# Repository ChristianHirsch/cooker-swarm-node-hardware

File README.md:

# cooker-swarm-node-hardware

This piece of hardware is used to control a induction hob remotely using a single board computer, a PC/notebook or a smartphone via Bluetooth Low Energy (BLE).

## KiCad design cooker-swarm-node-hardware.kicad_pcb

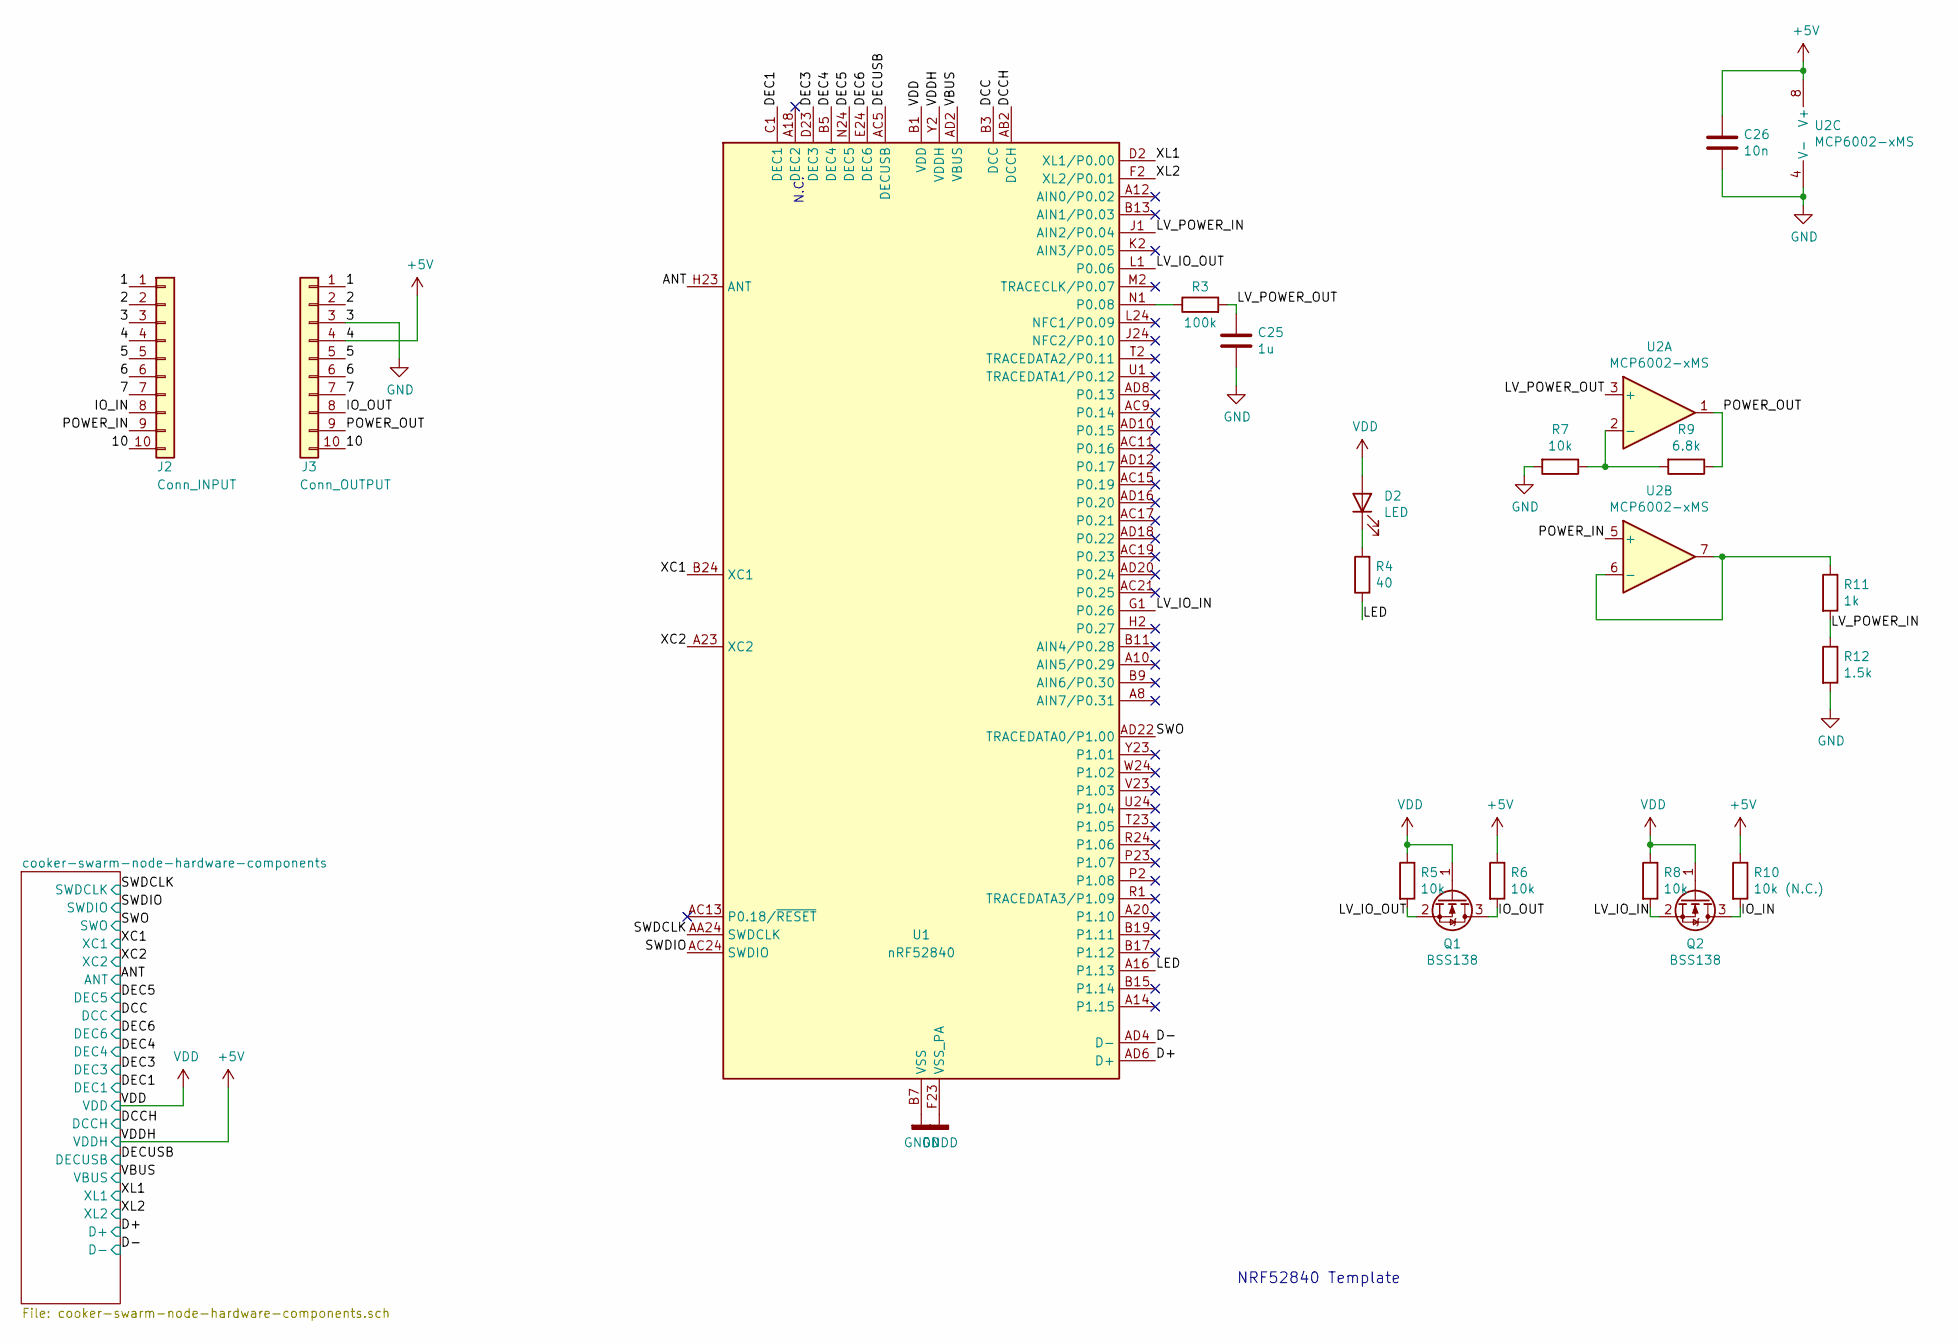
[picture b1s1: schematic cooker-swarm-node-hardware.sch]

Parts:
C25: 1u; C_0603_1608Metric
C26: 10n; C_0402_1005Metric
D2: LED; LED_1206_3216Metric
J2: Conn_INPUT; PinHeader_1x10_P2.54mm_Vertical
J3: Conn_OUTPUT; PinSocket_1x10_P2.54mm_Vertical
Q1, Q2: BSS138; SOT-23
R3: 100k; R_0402_1005Metric
R4: 40; R_0402_1005Metric
R5, R6, R7, R8: 10k; R_0402_1005Metric
R9: 6.8k; R_0402_1005Metric
R10: 10k (N.C.); R_0402_1005Metric
R11: 1k; R_0402_1005Metric
R12: 1.5k; R_0402_1005Metric
U1: nRF52840; Nordic_AQFN-73-1EP_7x7mm_P0.5mm
U2: MCP6002-xMS; MSOP-8_3x3mm_P0.65mm

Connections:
+5V: C26.1, J2.4, J3.4, R6.1, R10.1, U1.Y2 (VDDH), U2.8 (V+); also elsewhere on the board
/1: J2.1, J3.1
/2: J2.2, J3.2
/5: J2.5, J3.5
/6: J2.6, J3.6
/7: J2.7, J3.7
/10: J2.10, J3.10
/ANT: U1.H23 (ANT); also elsewhere on the board
/D+: U1.AD6 (D+); also elsewhere on the board
/D-: U1.AD4 (D-); also elsewhere on the board
/DCC: U1.B3 (DCC); also elsewhere on the board
/DCCH: U1.AB2 (DCCH); also elsewhere on the board
/DEC1: U1.C1 (DEC1); also elsewhere on the board
/DEC3: U1.D23 (DEC3); also elsewhere on the board
/DEC4: U1.B5 (DEC4), U1.E24 (DEC6); also elsewhere on the board
/DEC5: U1.N24 (DEC5); also elsewhere on the board
/DECUSB: U1.AC5 (DECUSB); also elsewhere on the board
/IO_IN: J2.8, Q2.3 (D), R10.2
/IO_OUT: J3.8, Q1.3 (D), R6.2
/LED: R4.1, U1.A16 (P1.13)
/LV_IO_IN: Q2.2 (S), R8.2, U1.G1 (P0.26)
/LV_IO_OUT: Q1.2 (S), R5.2, U1.L1 (P0.06)
/LV_POWER_IN: R11.2, R12.1, U1.J1 (AIN2/P0.04)
/LV_POWER_OUT: C25.1, R3.2, U2.3 (+)
/POWER_IN: J2.9, U2.5 (+)
/POWER_OUT: J3.9, R9.1, U2.1
/SWDCLK: U1.AA24 (SWDCLK); also elsewhere on the board
/SWDIO: U1.AC24 (SWDIO); also elsewhere on the board
/SWO: U1.AD22 (TRACEDATA0/P1.00); also elsewhere on the board
/XC1: U1.B24 (XC1); also elsewhere on the board
/XC2: U1.A23 (XC2); also elsewhere on the board
/XL1: U1.D2 (XL1/P0.00); also elsewhere on the board
/XL2: U1.F2 (XL2/P0.01); also elsewhere on the board
GND: C25.2, C26.2, J2.3, J3.3, R7.2, R12.2, U1.B7 (VSS), U1.EP (VSS), U1.F23 (VSS_PA), U2.4 (V-); also elsewhere on the board
unnamed: D2.1 (K), R4.2
unnamed: R3.1, U1.N1 (P0.08)
unnamed: R7.1, R9.2, U2.2 (-)
unnamed: R11.1, U2.6 (-), U2.7
VBUS: U1.AD2 (VBUS); also elsewhere on the board
VCC: D2.2 (A), Q1.1 (G), Q2.1 (G), R5.1, R8.1, U1.A22 (VDD), U1.AD14 (VDD), U1.AD23 (VDD), U1.B1 (VDD), U1.W1 (VDD); also elsewhere on the board

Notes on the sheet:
NRF52840 Template
N.C.

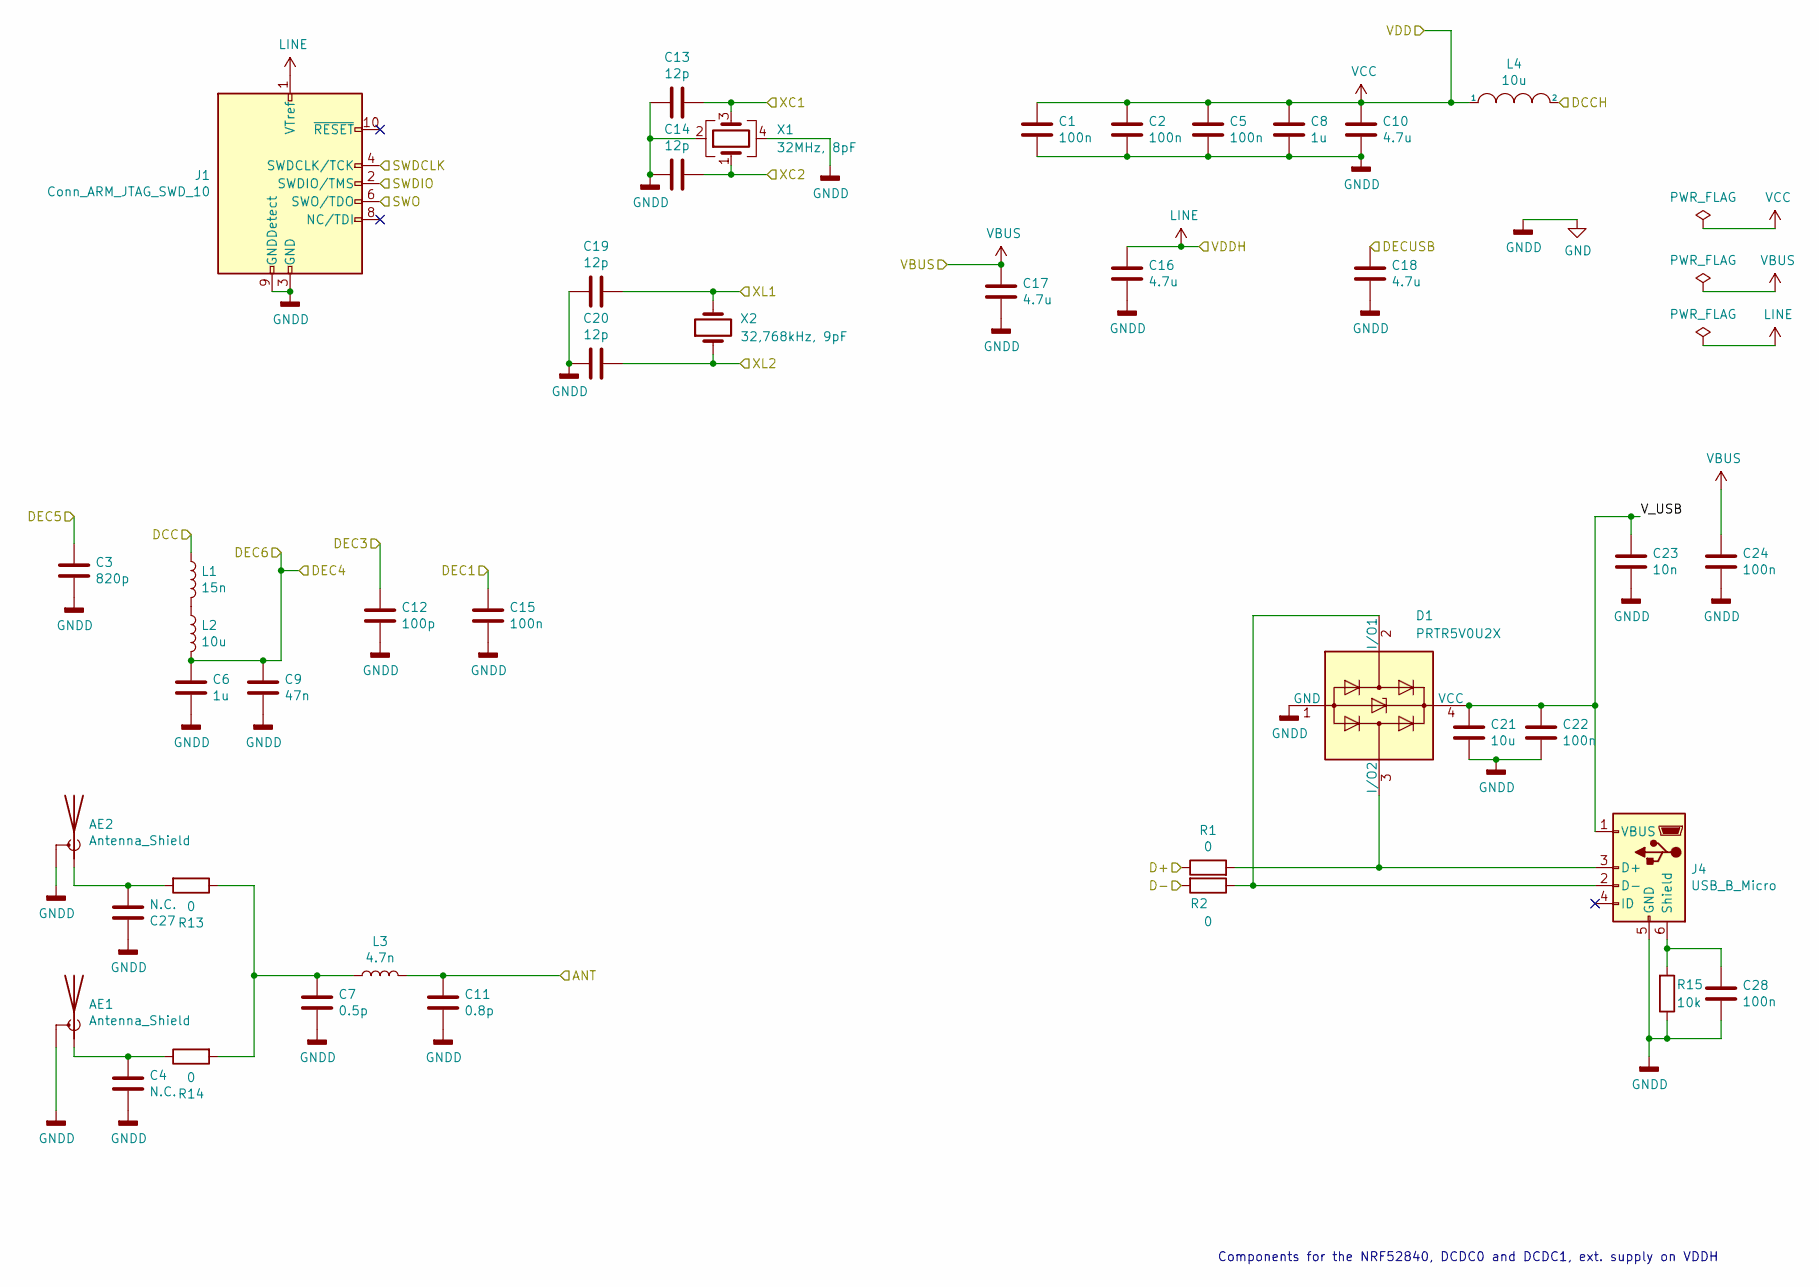
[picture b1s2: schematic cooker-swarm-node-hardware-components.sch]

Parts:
AE1: Antenna_Shield; Texas_SWRA117D_2.4GHz_Right
AE2: Antenna_Shield; U.FL_Molex_MCRF_73412-0110_Vertical
C1, C2, C5, C15, C22, C24, C28: 100n; C_0402_1005Metric
C3: 820p; C_0402_1005Metric
C4, C27: N.C.; C_0402_1005Metric
C6, C8: 1u; C_0603_1608Metric
C7: 0.5p; C_0402_1005Metric
C9: 47n; C_0402_1005Metric
C10, C16, C17, C18: 4.7u; C_0603_1608Metric
C11: 0.8p; C_0402_1005Metric
C12: 100p; C_0402_1005Metric
C13, C14, C19, C20: 12p; C_0402_1005Metric
C21: 10u; C_0603_1608Metric
C23: 10n; C_0402_1005Metric
D1: PRTR5V0U2X; SOT-143
J1: Conn_ARM_JTAG_SWD_10; PinHeader_2x05_P1.27mm_Vertical_SMD
J4: USB_B_Micro; USB_Micro-B_Molex_47346-0001
L1: 15n; L_0402_1005Metric
L2, L4: 10u; L_0603_1608Metric
L3: 4.7n; L_0402_1005Metric
R1, R2, R13, R14: 0; R_0402_1005Metric
R15: 10k; R_0402_1005Metric
X1: 32MHz, 8pF; Crystal_SMD_2016-4Pin_2.0x1.6mm
X2: 32,768kHz, 9pF; Crystal_SMD_3215-2Pin_3.2x1.5mm

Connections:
+5V: C16.1, J1.1 (VTref); also elsewhere on the board
/ANT: C11.1, L3.2; also elsewhere on the board
/D+: R1.1; also elsewhere on the board
/D-: R2.2; also elsewhere on the board
/DCC: L1.1; also elsewhere on the board
/DCCH: L4.2; also elsewhere on the board
/DEC1: C15.1; also elsewhere on the board
/DEC3: C12.1; also elsewhere on the board
/DEC4: C6.1, C9.1, L2.2; also elsewhere on the board
/DEC5: C3.1; also elsewhere on the board
/DECUSB: C18.1; also elsewhere on the board
/SWDCLK: J1.4 (SWDCLK/TCK); also elsewhere on the board
/SWDIO: J1.2 (SWDIO/TMS); also elsewhere on the board
/SWO: J1.6 (SWO/TDO); also elsewhere on the board
/XC1: C13.2, X1.3; also elsewhere on the board
/XC2: C14.2, X1.1; also elsewhere on the board
/XL1: C19.2, X2.2; also elsewhere on the board
/XL2: C20.2, X2.1; also elsewhere on the board
/cooker-swarm-node-hardware-components/V_USB: C21.1, C22.1, C23.1, D1.4 (VCC), J4.1 (VBUS)
GND: AE1.2 (Shield), AE2.2 (Shield), C1.2, C2.2, C3.2, C4.2, C5.2, C6.2, C7.2, C8.2, C9.2, C10.2, C11.2, C12.2, C13.1, C14.1, C15.2, C16.2, C17.2, C18.2, C19.1, C20.1, C21.2, C22.2, C23.2, C24.2, C27.1, C28.2, D1.1 (GND), J1.3 (GND), J1.5 (GND), J1.9 (GNDDetect), J4.5 (GND), R15.1, X1.2, X1.4; also elsewhere on the board
unnamed: AE1.1 (A), C4.1, R14.1
unnamed: AE2.1 (A), C27.2, R13.2
unnamed: C7.1, L3.1, R13.1, R14.2
unnamed: C28.1, J4.6 (Shield), R15.2
unnamed: D1.2 (I/O1), J4.2 (D-), R2.1
unnamed: D1.3 (I/O2), J4.3 (D+), R1.2
unnamed: L1.2, L2.1
VBUS: C17.1, C24.1; also elsewhere on the board
VCC: C1.1, C2.1, C5.1, C8.1, C10.1, L4.1; also elsewhere on the board

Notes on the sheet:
Components for the NRF52840, DCDC0 and DCDC1, ext. supply on VDDH

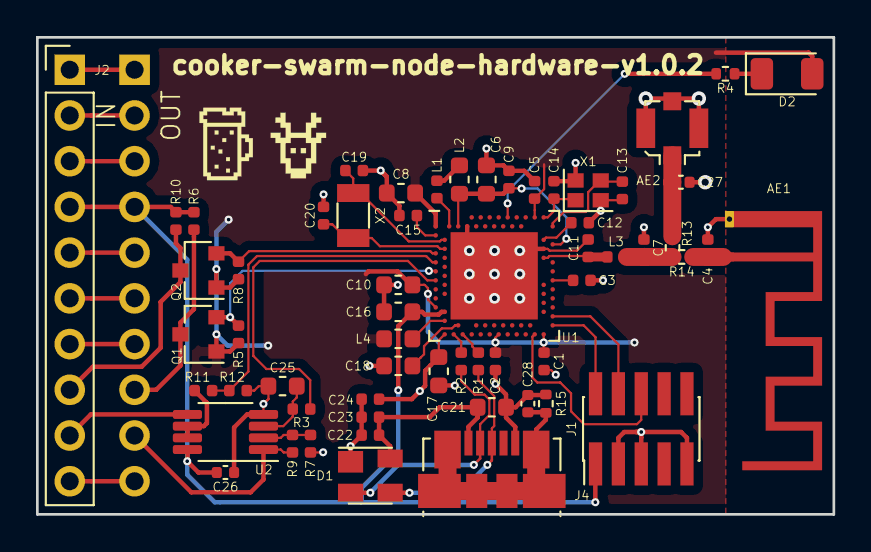
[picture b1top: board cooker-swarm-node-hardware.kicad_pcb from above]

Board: 2 copper layers, 44.2 x 26.5 mm, 61 parts (1 on the bottom side), 48 nets.

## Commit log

2020-01-24 use different footprint for operational amplifier
    makes soldering more easier
2022-05-04 use MCP6002 opamp
